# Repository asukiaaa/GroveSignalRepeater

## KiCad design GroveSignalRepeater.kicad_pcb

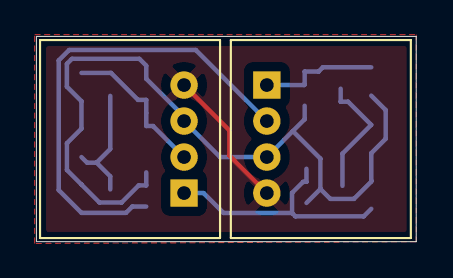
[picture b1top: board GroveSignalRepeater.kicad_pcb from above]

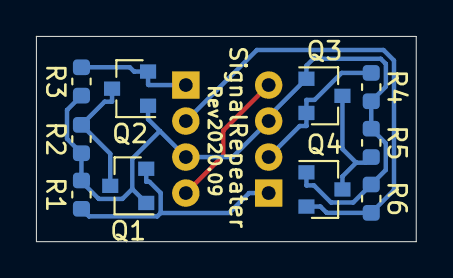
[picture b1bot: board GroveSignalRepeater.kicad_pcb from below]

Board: 2 copper layers, 21.1 x 11.4 mm, 12 parts (10 on the bottom side), 8 nets.

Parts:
J1, J2: Conn_01x04; NS-Tech_Grove_1x04_P2mm_Horizontal
Q1, Q2, Q3, Q4: Q_NMOS_GSD; SOT-23
R1, R2, R3, R4, R5, R6: 10k; R_0603_1608Metric

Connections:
/CON1_A: J1.1, Q1.2, R1.1
/CON1_B: J1.2, Q3.2, R4.1
/CON2_A: J2.1, Q2.2, R3.2
/CON2_B: J2.2, Q4.2, R6.2
GND: J1.4, J2.4
unnamed: Q1.3, Q2.3, R2.2
unnamed: Q3.3, Q4.3, R5.2
VCC: J1.3, J2.3, Q1.1, Q2.1, Q3.1, Q4.1, R1.2, R2.1, R3.1, R4.2, R5.1, R6.1

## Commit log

2020-10-05 Add size guide
